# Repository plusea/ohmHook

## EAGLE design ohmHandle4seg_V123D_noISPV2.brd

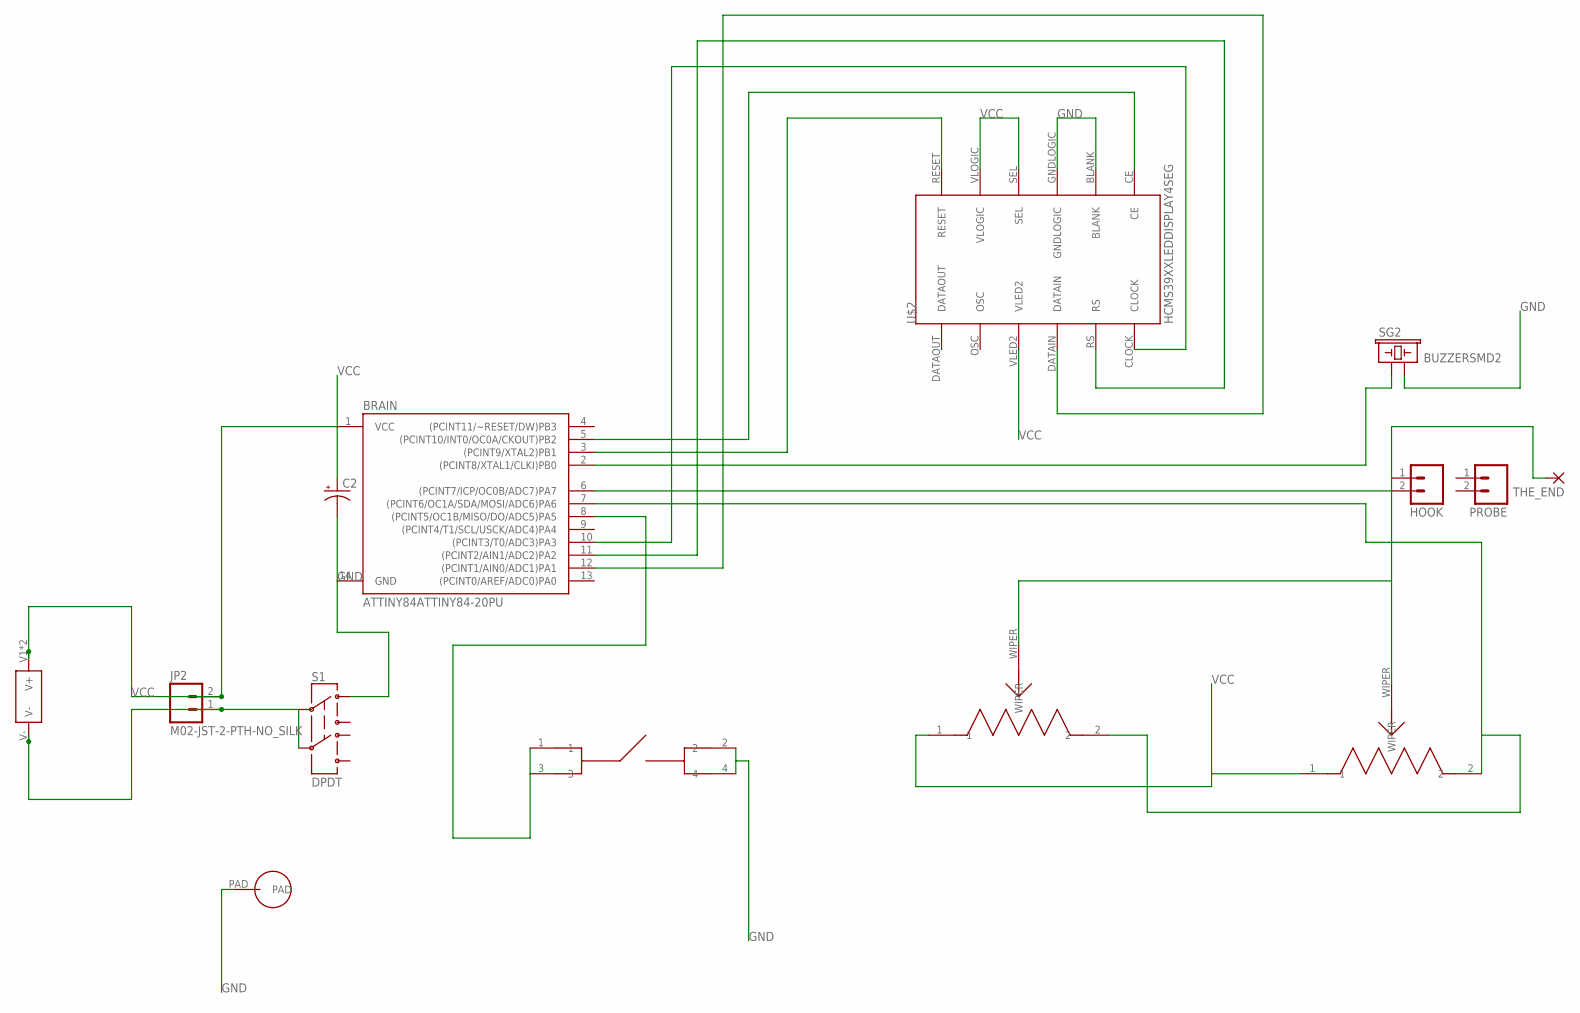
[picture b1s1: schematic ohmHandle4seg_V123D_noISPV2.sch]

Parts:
BRAIN: ATTINY84ATTINY84-20PU; DIL14
C2: CAP_POLPTH2; CPOL-RADIAL-10UF-25V
HOOK: M02LOCK_LONGPADS; 1X02_LOCK_LONGPADS
J1: HOLDER-BAT-D20.32; 2032-SMD-D20.32
JP2: M02-JST-2-PTH-NO_SILK; JST-2-PTH-NS
PROBE: M02LOCK_LONGPADS; 1X02_LOCK_LONGPADS
S1: DPDT; AYZ0202
SG2: BUZZERSMD2; BUZZER-CCV
THE_END: SMD5; SMD2,54-5,08
U$2: HCMS39XXLEDDISPLAY4SEG; LEDDISPLAY4SEG
U$3: THUMBPOT10MM
U$6: LARGEPAD
U$7: THUMBPOT3352; THUMBPOT3352P
U$9: BUTTONSMD; TACTILESWITCHSMD

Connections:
GND: BRAIN.14 (GND), C2.2 (-), S1.1, SG2.- (2), U$2.BLANK, U$2.GNDLOGIC, U$6.PAD, U$9.2, U$9.4
unnamed: BRAIN.3 ((PCINT9/XTAL2)PB1), U$2.RESET
unnamed: BRAIN.11 ((PCINT2/AIN1/ADC2)PA2), U$2.RS
unnamed: BRAIN.12 ((PCINT1/AIN0/ADC1)PA1), U$2.DATAIN
unnamed: BRAIN.8 ((PCINT5/OC1B/MISO/DO/ADC5)PA5), U$9.1, U$9.3
unnamed: J1.V-, JP2.1, S1.2, S1.5
unnamed: BRAIN.7 ((PCINT6/OC1A/SDA/MOSI/ADC6)PA6), U$3.2, U$7.2
unnamed: BRAIN.5 ((PCINT10/INT0/OC0A/CKOUT)PB2), U$2.CE
unnamed: BRAIN.10 ((PCINT3/T0/ADC3)PA3), U$2.CLOCK
unnamed: BRAIN.2 ((PCINT8/XTAL1/CLKI)PB0), SG2.+ (1)
THE_END: BRAIN.6 ((PCINT7/ICP/OC0B/ADC7)PA7), HOOK.1, HOOK.2, THE_END.1, U$3.WIPER, U$7.WIPER
VCC: BRAIN.1 (VCC), C2.1 (+), J1.V1 (V+), J1.V2 (V+), JP2.2, U$2.SEL, U$2.VLED2, U$2.VLOGIC, U$3.1, U$7.1

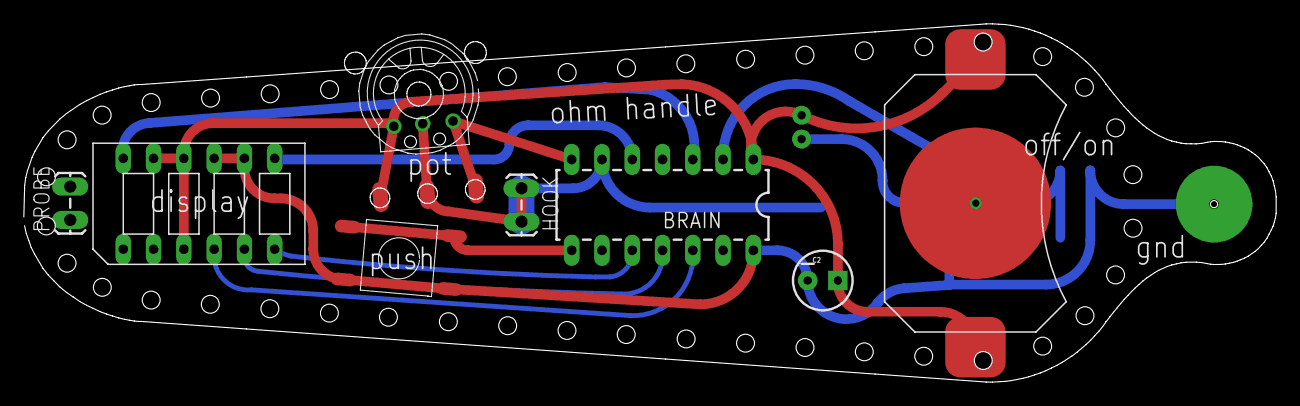
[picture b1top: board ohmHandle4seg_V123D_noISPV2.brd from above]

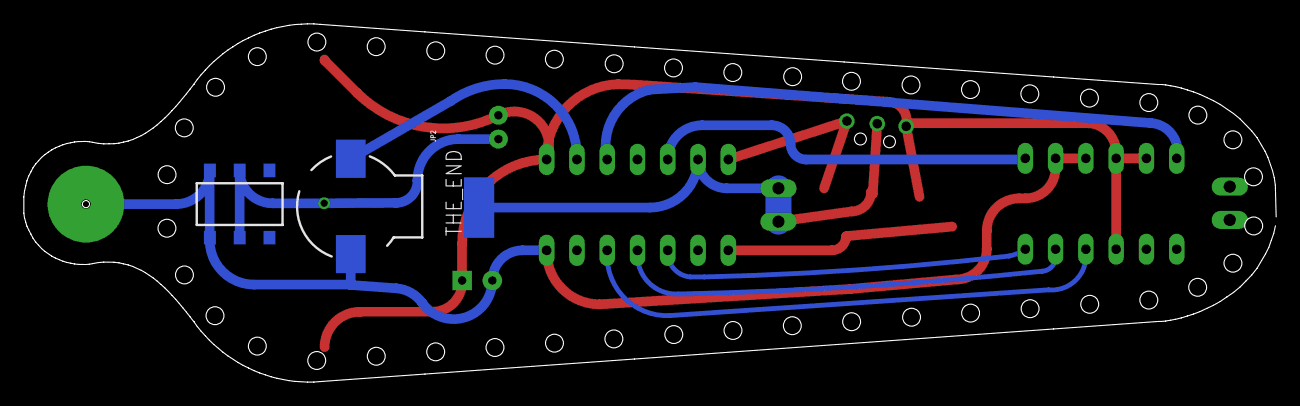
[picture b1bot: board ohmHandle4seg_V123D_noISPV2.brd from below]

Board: 2 copper layers, 105.1 x 30.1 mm, 15 parts (4 on the bottom side), 12 nets.

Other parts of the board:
U$1: OUTLINE4

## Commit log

2016-06-04 ohmHook code for eyeo workshop
2016-06-04 eagle files for eyeo workshop
2016-06-04 pdf of workshop booklet fo eyeo workshop
2016-06-04 cut file for panels and images of circuit
2016-08-21 added gitignore
2017-07-23 Added PDF files for those without Eagle ;-)
2017-07-24 Updated PDF with board layout to include names and values
2017-08-06 Code cleanup
2017-08-06 Moved Arduino source to subdirectory to make Arduino IDE happy
2017-08-06 Added option to read voltage.
2017-08-06 Restored brightness setting (was broken by previous commit)
2017-08-06 Attempt at improving resistance measurement (untested!)

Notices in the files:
parts and their libraries:
SparkFun-Passives: Licensing: Creative Commons ShareAlike 4.0 International - https://creativecommons.org/licenses/by-sa/4.0
